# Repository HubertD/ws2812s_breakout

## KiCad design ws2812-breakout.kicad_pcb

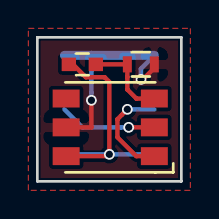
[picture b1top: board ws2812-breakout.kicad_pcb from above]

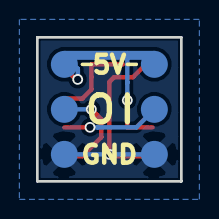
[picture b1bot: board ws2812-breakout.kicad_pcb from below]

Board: 2 copper layers, 8.0 x 8.0 mm, 9 parts (6 on the bottom side), 5 nets.

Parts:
C1: 100nF; C_0603
L1: WS2812S
R1: 100R; R_0603
W1: 5V_IN; Measurement_Point_Round-SMD-Pad_Small
W2: 5V_OUT; Measurement_Point_Round-SMD-Pad_Small
W3: GND_IN; Measurement_Point_Round-SMD-Pad_Small
W4: GND_OUT; Measurement_Point_Round-SMD-Pad_Small
W5: DIN; Measurement_Point_Round-SMD-Pad_Small
W6: DOUT; Measurement_Point_Round-SMD-Pad_Small

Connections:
+5V: L1.5, R1.1, W1.1, W2.1
GND: C1.2, L1.6, W3.1, W4.1
unnamed: C1.1, L1.3, R1.2
unnamed: L1.1, W6.1
unnamed: L1.2, W5.1

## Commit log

2016-06-05 initial checkin
